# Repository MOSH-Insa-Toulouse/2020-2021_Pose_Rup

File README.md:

# 2020-2021_Pose_Rup
Shield comportant un capteur de gaz développé à l'AIME pour la Arduino UNO

## SMALL DESCRIPTION
Ce shield permet l'exploitation directe de la mesure du gas dans un pièce grâce au capteur de gas développé en salle blanche à l'AIME.
Une LED rouge permet de prévenir lutilisateur d'une trop mauvaise qualité de l'air.
Un espace a été spécialement réservé pour inclure la carte de développement du module RN2483A de drazzy.com.

---

## INCLUDE IN THE DESIGN

- [x] Gas sensor réalisé à l'AIME
- [x] Capteur de température pour mesurer la température opérationelle du capteur de gas
- [x] Circuit de traitement et amplification du signal du capteur de gaz
- [x] LED rouge pour prévenir l'utilisateur d'un danger / mauvaise qualité de l'air
- [x] Socket pour venir fixer la carte intégrant le module LoRa et son antenne
- [x] 2 transistors NPN permettant d'allumer ou d'éteindre les alimentations du circuit capteur (entre 2 prises de mesure) en utilisant la pin 3 de l'Arduino

## Bill Of Materials

|           Components           |             Reference            |
|:------------------------------:|:--------------------------------:|
| Gas sensor                     | GSWO3AIME20 (built at AIME)      |
| Operational Amplifier          | LTC1050                          |
| NPN transistor                 | P2N2222A                         |
| LoRa module                    | RN2483                           |
| External Board for LoRa module | Drazzy.com RN2483 Breakout Board |

---

## Tools used

### KiCad

[KiCad EDA - Schematic Capture & PCB Design Software](https://kicad-pcb.org/), version: 5.1.7

Open source EDA / electronics CAD software for Windows, macOS and Linux.

## Electrical diagram

## Components placement

## 3D view

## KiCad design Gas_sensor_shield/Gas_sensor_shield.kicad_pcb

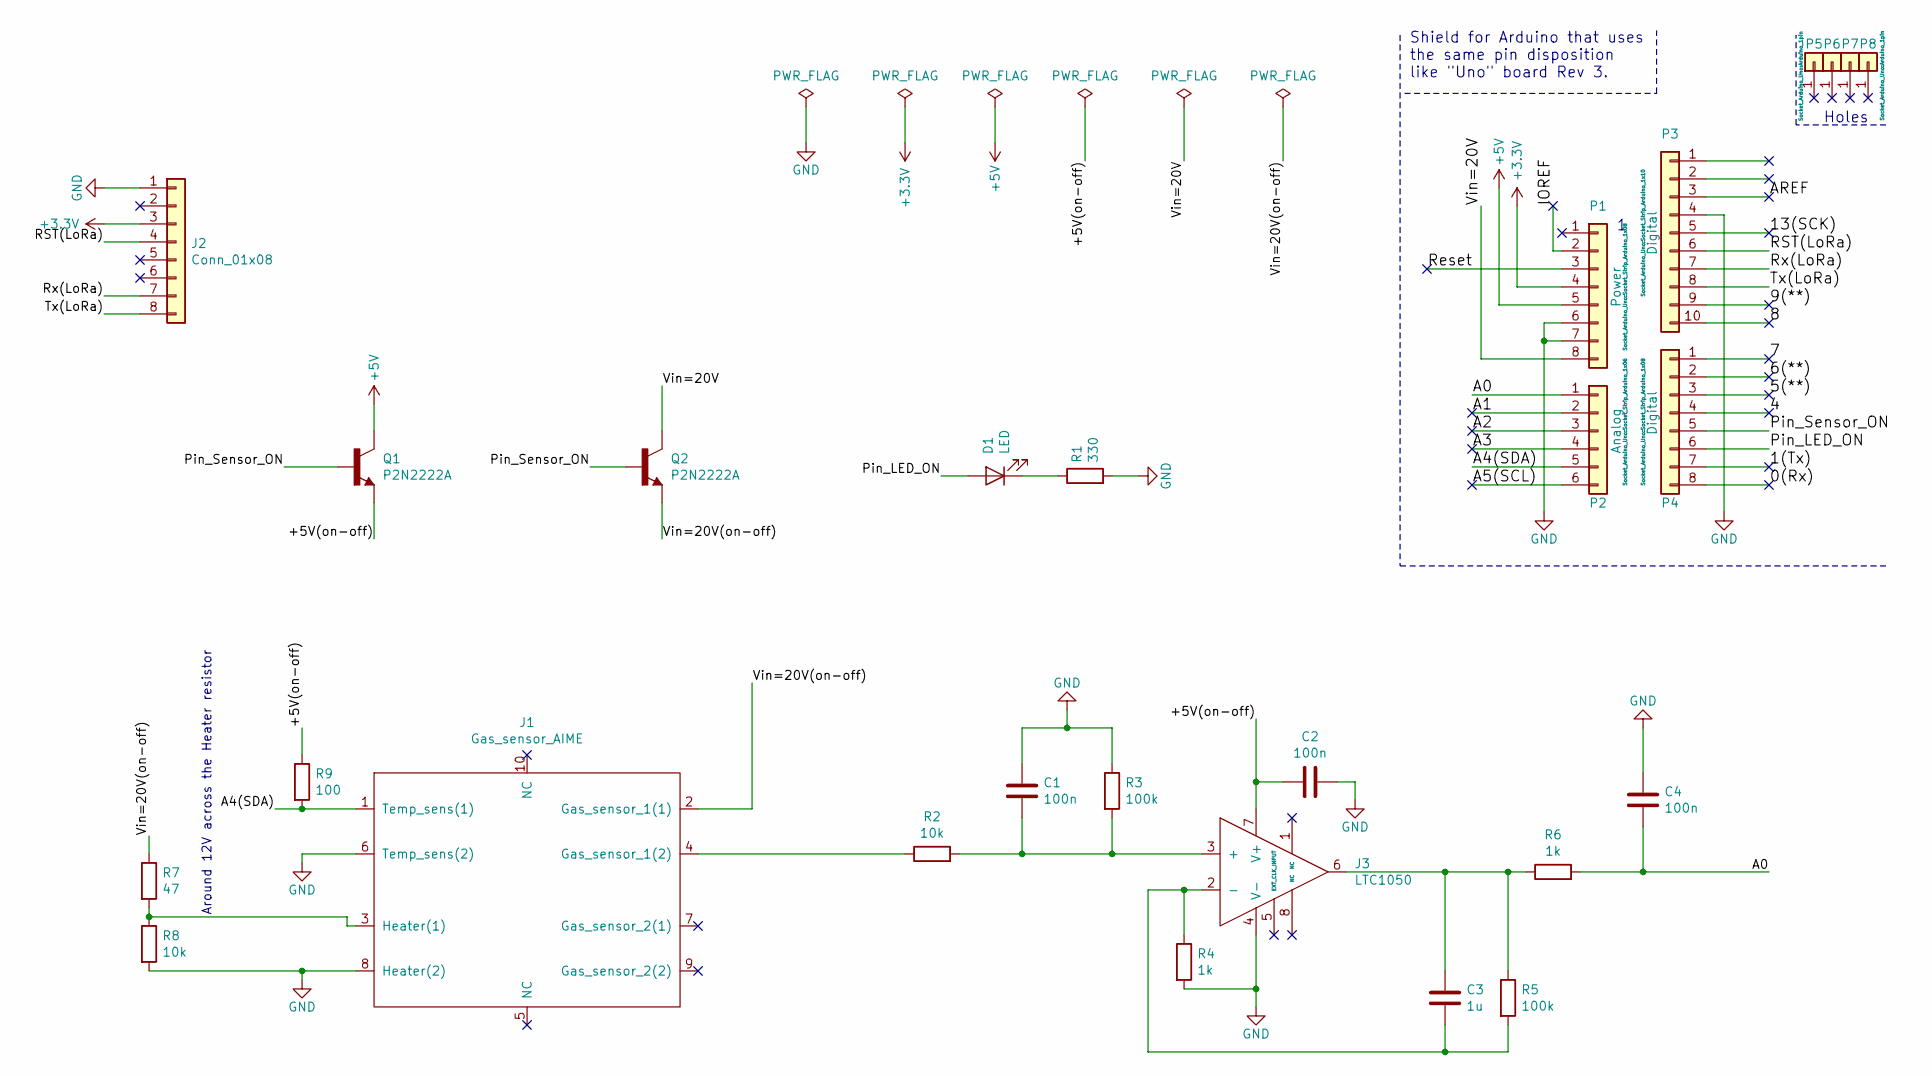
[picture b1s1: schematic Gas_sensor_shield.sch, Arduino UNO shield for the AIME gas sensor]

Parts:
C1, C2, C4: 100n; CP_Radial_Tantal_D5.5mm_P5.00mm
C3: 1u; CP_Radial_Tantal_D5.5mm_P5.00mm
D1: LED; LED_D5.0mm
J1: Gas_sensor_AIME; Package_TO-5-10_Window
J2: Conn_01x08; PinSocket_1x08_P2.54mm_Vertical
J3: LTC1050; Package_DIP-8_W7.62mm_LongPads
P1: Power; Socket_Strip_Arduino_1x08
P2: Analog; Socket_Strip_Arduino_1x06
P3: Digital; Socket_Strip_Arduino_1x10
P4: Digital; Socket_Strip_Arduino_1x08
P5, P6, P7, P8: CONN_01X01; Arduino_1pin
Q1, Q2: P2N2222A; Package_TO-92
R1: 330; R_Axial_DIN0207_L6.3mm_D2.5mm_P10.16mm_Horizontal
R2, R8: 10k; R_Axial_DIN0207_L6.3mm_D2.5mm_P10.16mm_Horizontal
R3, R5: 100k; R_Axial_DIN0207_L6.3mm_D2.5mm_P10.16mm_Horizontal
R4, R6: 1k; R_Axial_DIN0207_L6.3mm_D2.5mm_P10.16mm_Horizontal
R7: 47; R_Axial_DIN0207_L6.3mm_D2.5mm_P10.16mm_Horizontal
R9: 100; R_Axial_DIN0207_L6.3mm_D2.5mm_P10.16mm_Horizontal

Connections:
+3V3: J2.3, P1.4
+5V: P1.5, Q1.3
/0(Rx): P4.8
/1(Tx): P4.7
/4: P4.4
/5(**): P4.3
/6(**): P4.2
/7: P4.1
/8: P3.10
/9(**): P3.9
/13(SCK): P3.5
/+5V(on-off): C2.2, J3.7 (V+), Q1.1, R9.1
/A0: C4.2, P2.1, R6.2
/A1: P2.2
/A2: P2.3
/A3: P2.4
/A4(SDA): J1.1 (Temp_sens(1)), P2.5, R9.2
/A5(SCL): P2.6
/AREF: P3.3
/IOREF: P1.2
/Pin_LED_ON: D1.2 (A), P4.6
/Pin_Sensor_ON: P4.5, Q1.2, Q2.2
/RST(LoRa): J2.4, P3.6
/Reset: P1.3
/Rx(LoRa): J2.7, P3.7
/Tx(LoRa): J2.8, P3.8
/Vin=20V: P1.8, Q2.3
/Vin=20V(on-off): J1.2 (Gas_sensor_1(1)), Q2.1, R7.1
GND: C1.1, C2.1, C4.1, J1.6 (Temp_sens(2)), J1.8 (Heater(2)), J2.1, J3.4 (V-), P1.6, P1.7, P3.4, R1.2, R3.1, R4.2, R8.2
unnamed: C1.2, J3.3 (+), R2.2, R3.2
unnamed: C3.1, J3.6, R5.1, R6.1
unnamed: C3.2, J3.2 (-), R4.1, R5.2
unnamed: D1.1 (K), R1.1
unnamed: J1.3 (Heater(1)), R7.2, R8.1
unnamed: J1.4 (Gas_sensor_1(2)), R2.1

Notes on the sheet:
Holes
Shield for Arduino that uses the same pin disposition like "Uno" board Rev 3.
Around 12V across the Heater resistor

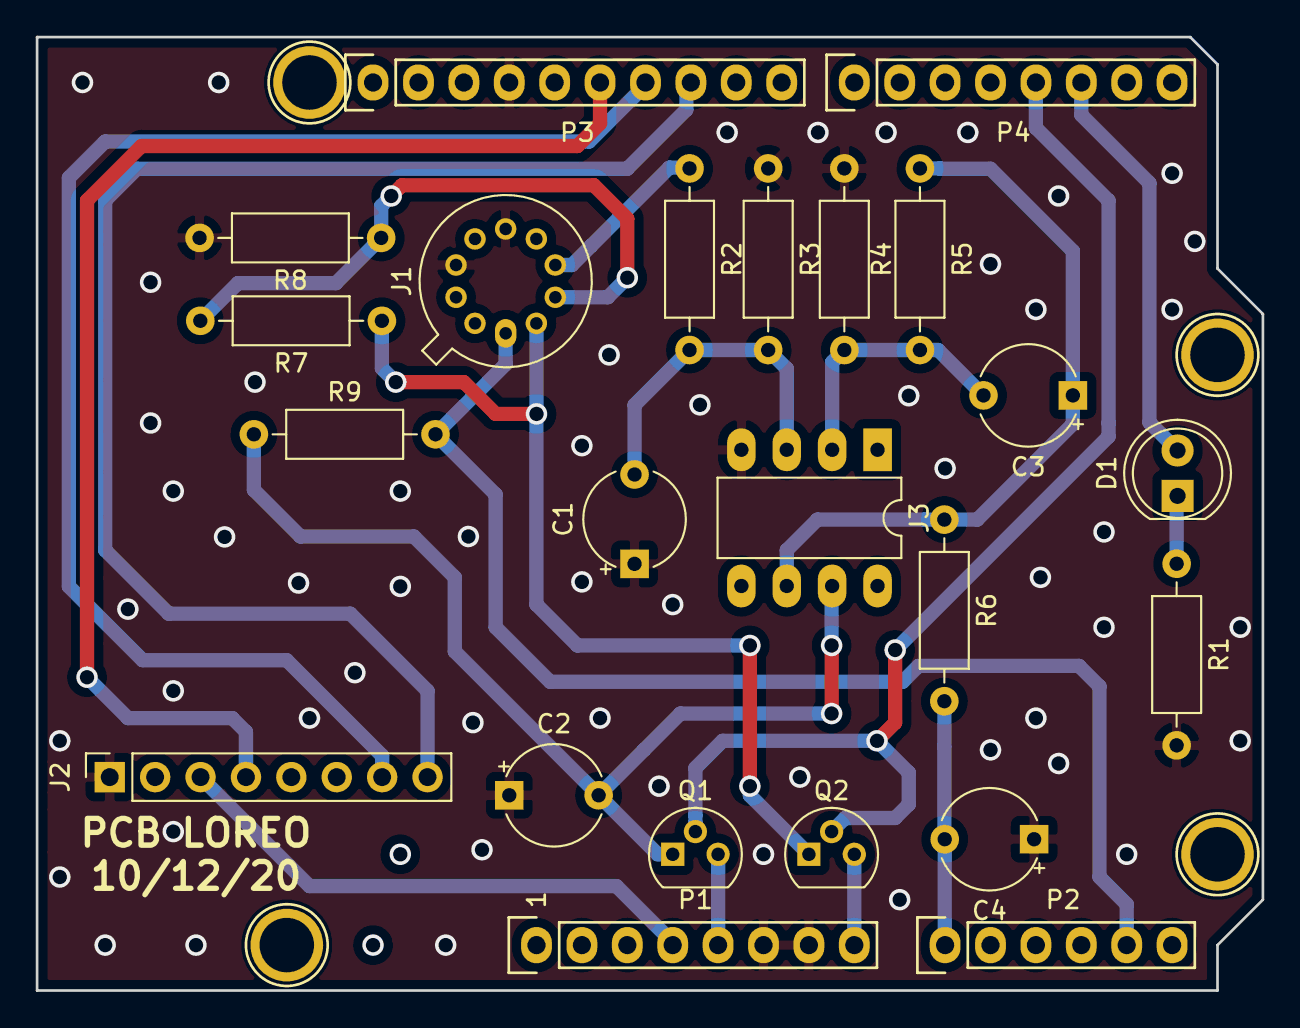
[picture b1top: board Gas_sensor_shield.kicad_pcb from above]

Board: 2 copper layers, 68.6 x 53.3 mm, 27 parts (0 on the bottom side), 19 nets.

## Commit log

2020-12-07 Première version du PCB
2020-12-07 Rectification du path des images du Readme
2020-12-07 Proposition de correction
2020-12-10 Correction librairies
2020-12-10 Corrections du board
2020-12-10 Correction du board
2020-12-10 Attache image board readme.md
2020-12-10 Schema modification
2020-12-11 Add BOM
